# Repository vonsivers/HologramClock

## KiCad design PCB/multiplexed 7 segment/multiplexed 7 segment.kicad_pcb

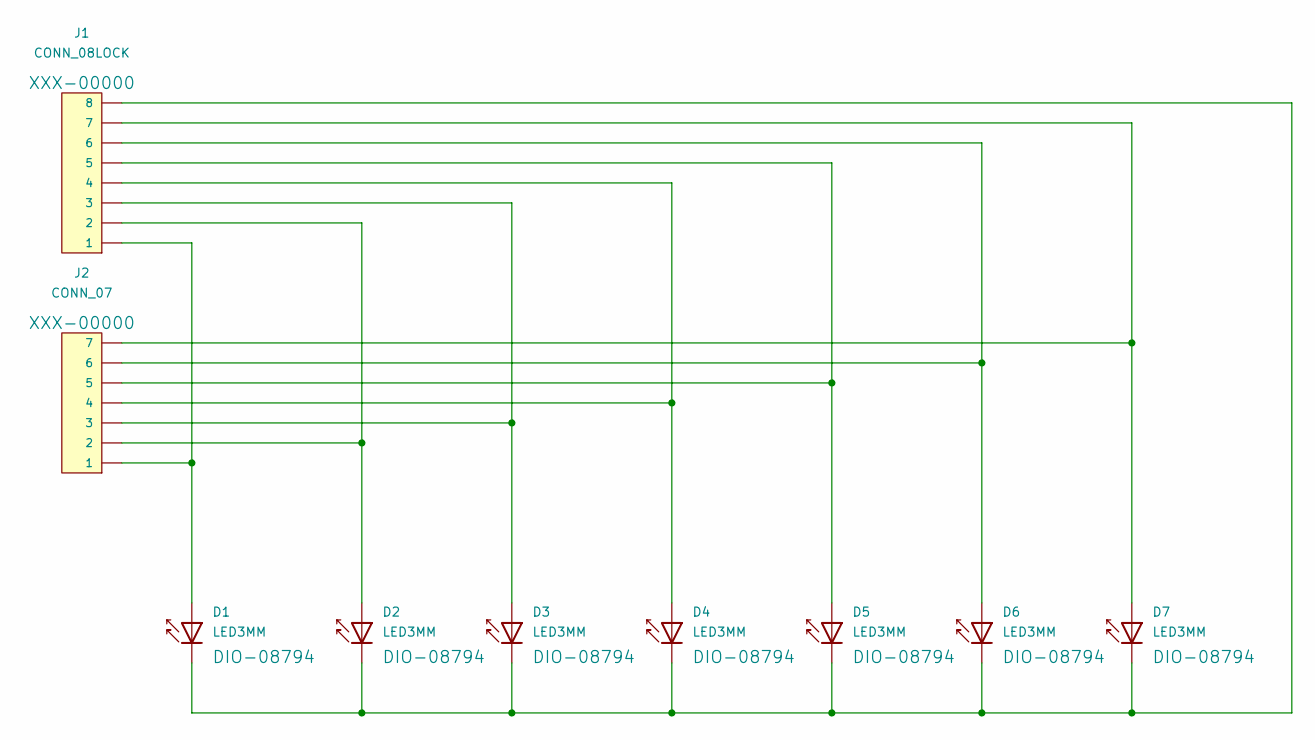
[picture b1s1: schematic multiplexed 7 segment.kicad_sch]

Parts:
D1, D2, D3, D4, D5, D6, D7: LED3MM; LED_D3.0mm
J1: CONN_08LOCK; PinHeader_1x08_P2.54mm_Vertical
J2: CONN_07; PinHeader_1x08_P2.54mm_Vertical

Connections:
unnamed: D1.1 (K), D2.1 (K), D3.1 (K), D4.1 (K), D5.1 (K), D6.1 (K), D7.1 (K), J1.8
unnamed: D1.2 (A), J1.1, J2.1
unnamed: D2.2 (A), J1.2, J2.2
unnamed: D3.2 (A), J1.3, J2.3
unnamed: D4.2 (A), J1.4, J2.4
unnamed: D5.2 (A), J1.5, J2.5
unnamed: D6.2 (A), J1.6, J2.6
unnamed: D7.2 (A), J1.7, J2.7

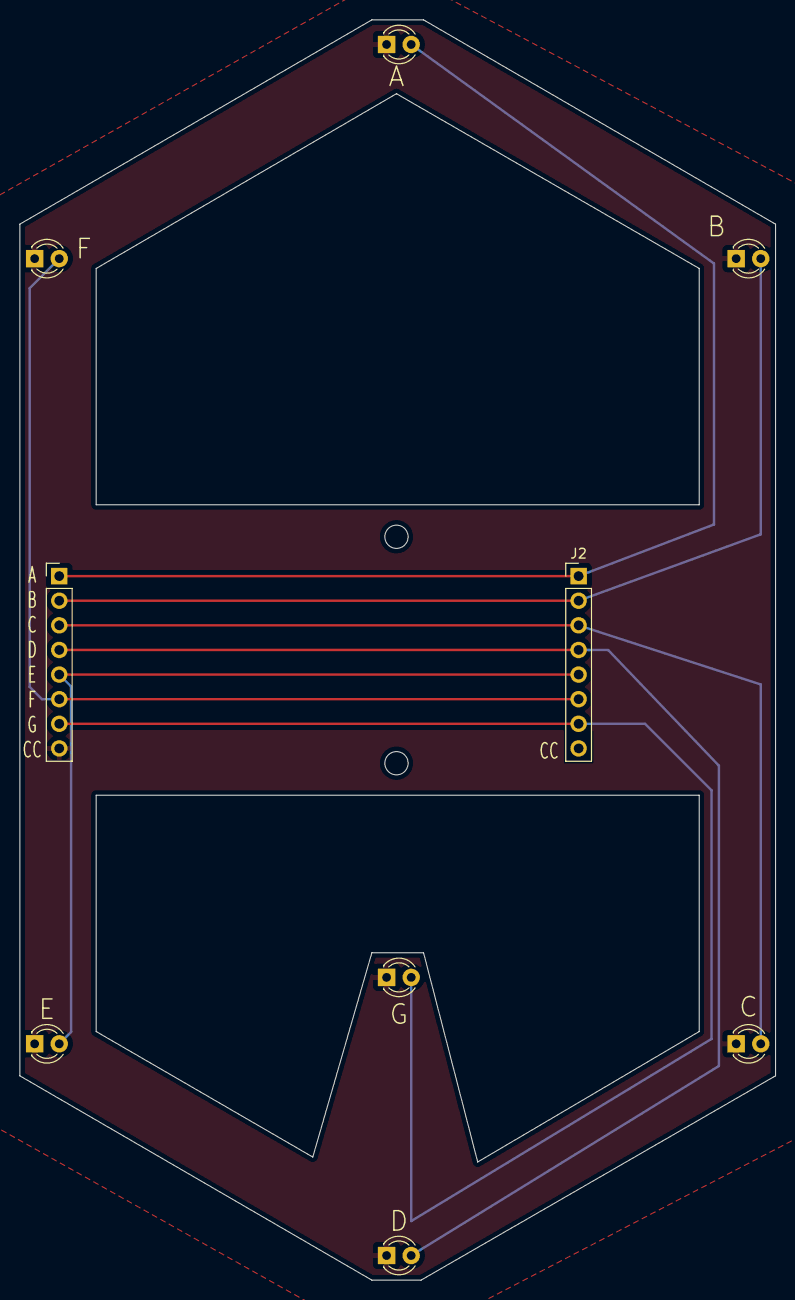
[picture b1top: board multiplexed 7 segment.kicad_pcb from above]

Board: 2 copper layers, 78.0 x 130.0 mm, 9 parts (0 on the bottom side), 8 nets.

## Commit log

2025-11-23 added dxf
2025-11-23 added wiring schematics and recording steps
2026-05-14 Update HologramClock.ino
    correct use of DST
